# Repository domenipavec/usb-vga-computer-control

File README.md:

# usb-vga-computer-control

## Installation

`sudo apt-get install python-opencv v4l-utils python-pip`
`sudo pip install -r python-software/requirements.txt`

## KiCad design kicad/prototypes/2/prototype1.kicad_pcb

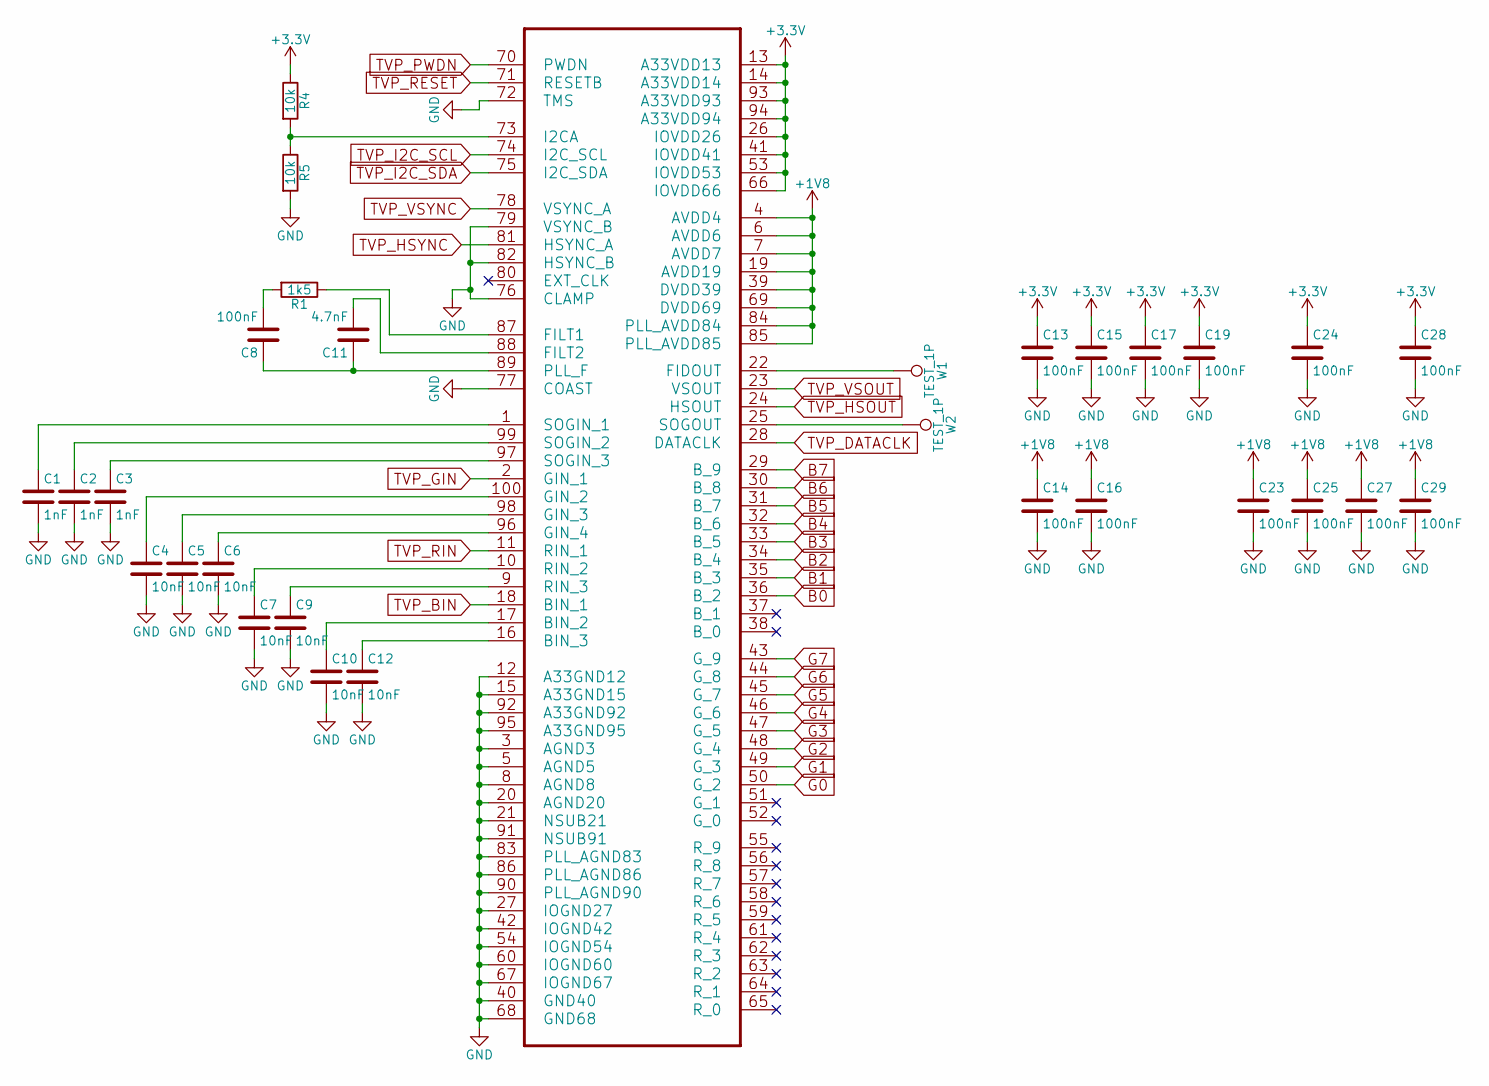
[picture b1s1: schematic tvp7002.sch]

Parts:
C1, C2, C3: 1nF; C_0402
C4, C5, C6, C7, C9, C10, C12: 10nF; C_0402
C8, C13, C14, C15, C16, C17, C19, C23, C24, C25, C27, C28, C29: 100nF; C_0402
C11: 4.7nF; C_0805
R1: 1k5; R_0805
R4, R5: 10k; R_0805
U1: TVP7002; LQFP-100_14x14mm_Pitch0.5mm
W1, W2: TEST_1P; Measurement_Point_Round-SMD-Pad_Small

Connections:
+1V8: C14.1, C16.1, C23.1, C25.1, C27.1, C29.1, U1.4 (AVDD4), U1.6 (AVDD6), U1.7 (AVDD7), U1.19 (AVDD19), U1.39 (DVDD39), U1.69 (DVDD69), U1.84 (PLL_AVDD84), U1.85 (PLL_AVDD85); also elsewhere on the board
+3V3: C13.1, C15.1, C17.1, C19.1, C24.1, C28.1, R4.1, U1.13 (A33VDD13), U1.14 (A33VDD14), U1.26 (IOVDD26), U1.41 (IOVDD41), U1.53 (IOVDD53), U1.66 (IOVDD66), U1.93 (A33VDD93), U1.94 (A33VDD94); also elsewhere on the board
B0: U1.36 (B_2); also elsewhere on the board
B1: U1.35 (B_3); also elsewhere on the board
B2: U1.34 (B_4); also elsewhere on the board
B3: U1.33 (B_5); also elsewhere on the board
B4: U1.32 (B_6); also elsewhere on the board
B5: U1.31 (B_7); also elsewhere on the board
B6: U1.30 (B_8); also elsewhere on the board
B7: U1.29 (B_9); also elsewhere on the board
G0: U1.50 (G_2); also elsewhere on the board
G1: U1.49 (G_3); also elsewhere on the board
G2: U1.48 (G_4); also elsewhere on the board
G3: U1.47 (G_5); also elsewhere on the board
G4: U1.46 (G_6); also elsewhere on the board
G5: U1.45 (G_7); also elsewhere on the board
G6: U1.44 (G_8); also elsewhere on the board
G7: U1.43 (G_9); also elsewhere on the board
GND: C1.2, C2.2, C3.2, C4.2, C5.2, C6.2, C7.2, C9.2, C10.2, C12.2, C13.2, C14.2, C15.2, C16.2, C17.2, C19.2, C23.2, C24.2, C25.2, C27.2, C28.2, C29.2, R5.2, U1.3 (AGND3), U1.5 (AGND5), U1.8 (AGND8), U1.12 (A33GND12), U1.15 (A33GND15), U1.20 (AGND20), U1.21 (NSUB21), U1.27 (IOGND27), U1.40 (GND40), U1.42 (IOGND42), U1.54 (IOGND54), U1.60 (IOGND60), U1.67 (IOGND67), U1.68 (GND68), U1.72 (TMS), U1.76 (CLAMP), U1.77 (COAST), U1.79 (VSYNC_B), U1.82 (HSYNC_B), U1.83 (PLL_AGND83), U1.86 (PLL_AGND86), U1.90 (PLL_AGND90), U1.91 (NSUB91), U1.92 (A33GND92), U1.95 (A33GND95); also elsewhere on the board
unnamed: C1.1, U1.1 (SOGIN_1)
unnamed: C2.1, U1.99 (SOGIN_2)
unnamed: C3.1, U1.97 (SOGIN_3)
unnamed: C4.1, U1.100 (GIN_2)
unnamed: C5.1, U1.98 (GIN_3)
unnamed: C6.1, U1.96 (GIN_4)
unnamed: C7.1, U1.10 (RIN_2)
unnamed: C8.2, R1.2
unnamed: C9.1, U1.9 (RIN_3)
unnamed: C10.1, U1.17 (BIN_2)
unnamed: C8.1, C11.1, U1.89 (PLL_F)
unnamed: C11.2, U1.88 (FILT2)
unnamed: C12.1, U1.16 (BIN_3)
unnamed: R1.1, U1.87 (FILT1)
unnamed: R4.2, R5.1, U1.73 (I2CA)
unnamed: U1.22 (FIDOUT), W1.1
unnamed: U1.25 (SOGOUT), W2.1
TVP_BIN: U1.18 (BIN_1); also elsewhere on the board
TVP_DATACLK: U1.28 (DATACLK); also elsewhere on the board
TVP_GIN: U1.2 (GIN_1); also elsewhere on the board
TVP_HSOUT: U1.24 (HSOUT); also elsewhere on the board
TVP_HSYNC: U1.81 (HSYNC_A); also elsewhere on the board
TVP_I2C_SCL: U1.74 (I2C_SCL); also elsewhere on the board
TVP_I2C_SDA: U1.75 (I2C_SDA); also elsewhere on the board
TVP_PWDN: U1.70 (PWDN); also elsewhere on the board
TVP_RESET: U1.71 (RESETB); also elsewhere on the board
TVP_RIN: U1.11 (RIN_1); also elsewhere on the board
TVP_VSOUT: U1.23 (VSOUT); also elsewhere on the board
TVP_VSYNC: U1.78 (VSYNC_A); also elsewhere on the board

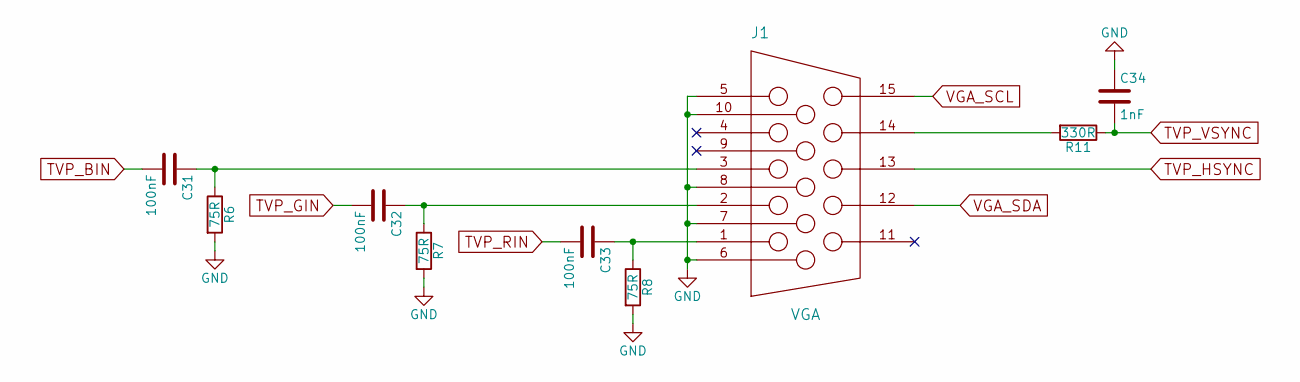
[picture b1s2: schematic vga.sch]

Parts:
C31, C32, C33: 100nF; C_0402
C34: 1nF; C_0402
J1: VGA
R6, R7, R8: 75R; R_0805
R11: 330R; R_0805

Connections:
AVR_MOSI: J1.12 (ID1/SDA); also elsewhere on the board
AVR_SCK: J1.15 (ID3/SCL); also elsewhere on the board
GND: C34.1, J1.5 (GND_HSYNC), J1.6 (RED_RTN), J1.7 (GREEN_RTN), J1.8 (BLUE_RTN), J1.10 (GND_VSYNC), R6.2, R7.2, R8.2; also elsewhere on the board
unnamed: C31.1, J1.3 (BLUE), R6.1
unnamed: C32.1, J1.2 (GREEN), R7.1
unnamed: C33.1, J1.1 (RED), R8.1
unnamed: J1.14 (VSYNC), R11.2
TVP_BIN: C31.2; also elsewhere on the board
TVP_GIN: C32.2; also elsewhere on the board
TVP_HSYNC: J1.13 (HSYNC); also elsewhere on the board
TVP_RIN: C33.2; also elsewhere on the board
TVP_VSYNC: C34.2, R11.1; also elsewhere on the board

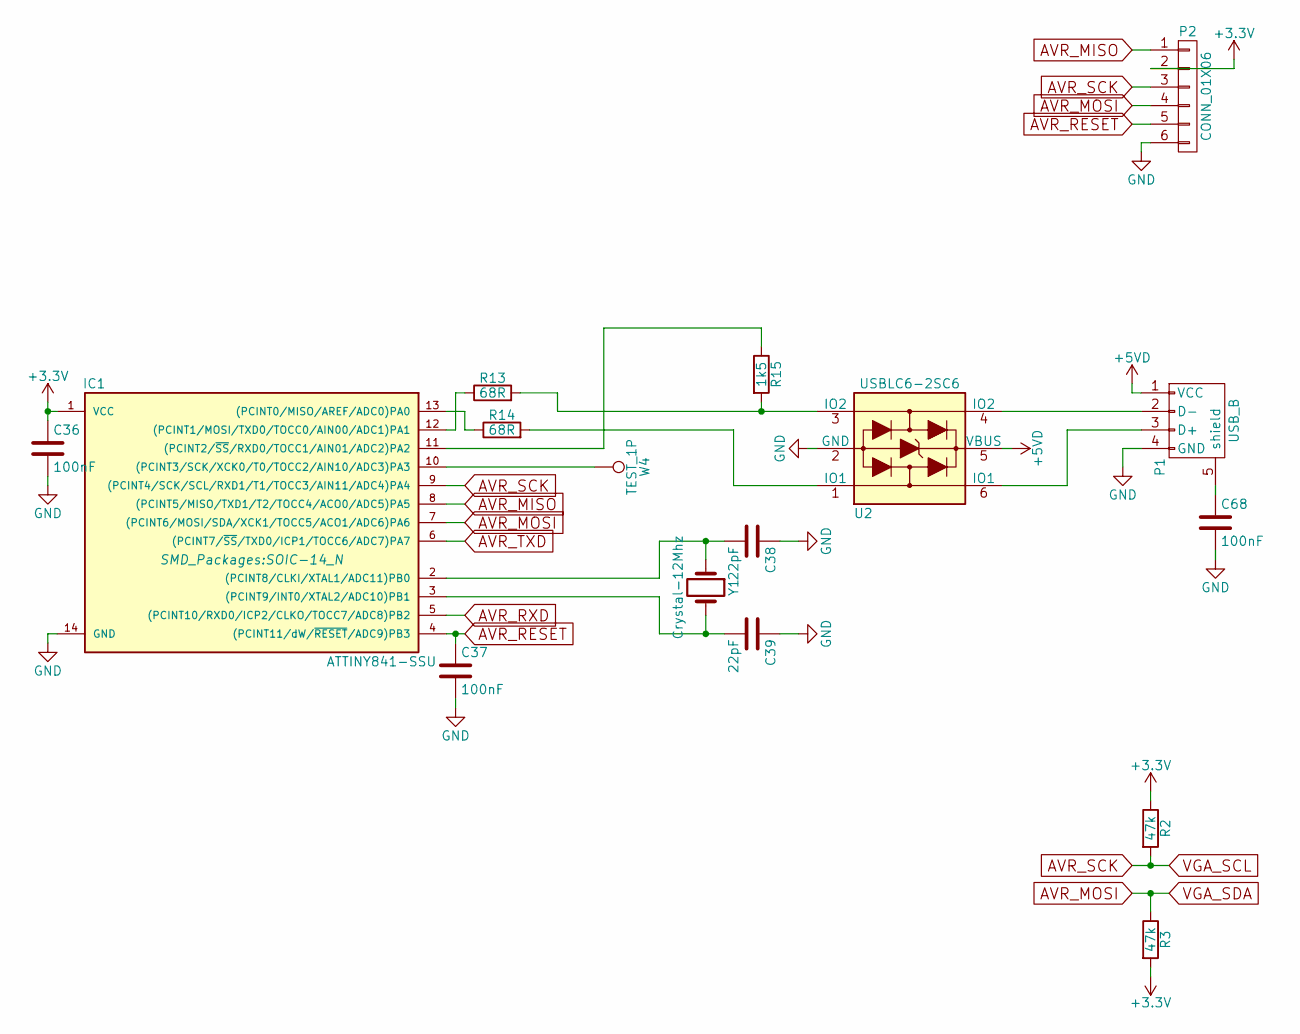
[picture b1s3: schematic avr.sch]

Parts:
C36, C37, C68: 100nF; C_0402
C38, C39: 22pF; C_0805
IC1: ATTINY841-SSU; SOIC-14_N
P1: USB_B
P2: CONN_01X06; ATTINY841-SPI
R2, R3: 47k; R_0805
R13, R14: 68R; R_0805
R15: 1k5; R_0805
U2: USBLC6-2SC6; SOT-23-6
W4: TEST_1P; Measurement_Point_Round-SMD-Pad_Small
Y1: Crystal-12Mhz; Crystal_HC49-U_Vertical

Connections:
+3V3: C36.1, IC1.1 (VCC), P2.2, R2.1, R3.2; also elsewhere on the board
+5VD: P1.1 (VCC), U2.5 (VBUS)
AVR_MISO: IC1.8 ((PCINT5/MISO/TXD1/T2/TOCC4/ACO0/ADC5)PA5), P2.1
AVR_MOSI: IC1.7 ((PCINT6/MOSI/SDA/XCK1/TOCC5/ACO1/ADC6)P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), P2.4, R3.1; also elsewhere on the board
AVR_RESET: C37.1, IC1.4 ((PCINT11/dW/~RESET~/ADC9)PB3), P2.5
AVR_RXD: IC1.5 ((PCINT10/RXD0/ICP2/CLKO/TOCC7/ADC8)PB2); also elsewhere on the board
AVR_SCK: IC1.9 ((PCINT4/SCK/SCL/RXD1/T1/TOCC3/AIN11/ADC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), P2.3, R2.2; also elsewhere on the board
AVR_TXD: IC1.6 ((PCINT7/~SS~/TXD0/ICP1/TOCC6/ADC7)PA7); also elsewhere on the board
GND: C36.2, C37.2, C38.1, C39.1, C68.2, IC1.14 (GND), P1.4 (GND), P2.6, U2.2 (GND); also elsewhere on the board
unnamed: C38.2, IC1.2 ((PCINT8/CLKI/XTAL1/ADC11)PB0), Y1.1
unnamed: C39.2, IC1.3 ((PCINT9/INT0/XTAL2/ADC10)PB1), Y1.2
unnamed: C68.1, P1.5 (shield)
unnamed: IC1.10 ((PCINT3/SCK/XCK0/T0/TOCC2/AIN10/ADC3)PA3), W4.1
unnamed: IC1.11 ((PCINT2/~SS~/RXD0/TOCC1/AIN01/ADC2)PA2), R15.1
unnamed: IC1.12 ((PCINT1/MOSI/TXD0/TOCC0/AIN00/ADC1)PA1), R13.1
unnamed: IC1.13 ((PCINT0/MISO/AREF/ADC0)PA0), R14.1
unnamed: P1.2 (D-), U2.4 (IO2)
unnamed: P1.3 (D+), U2.6 (IO1)
unnamed: R13.2, R15.2, U2.3 (IO2)
unnamed: R14.2, U2.1 (IO1)

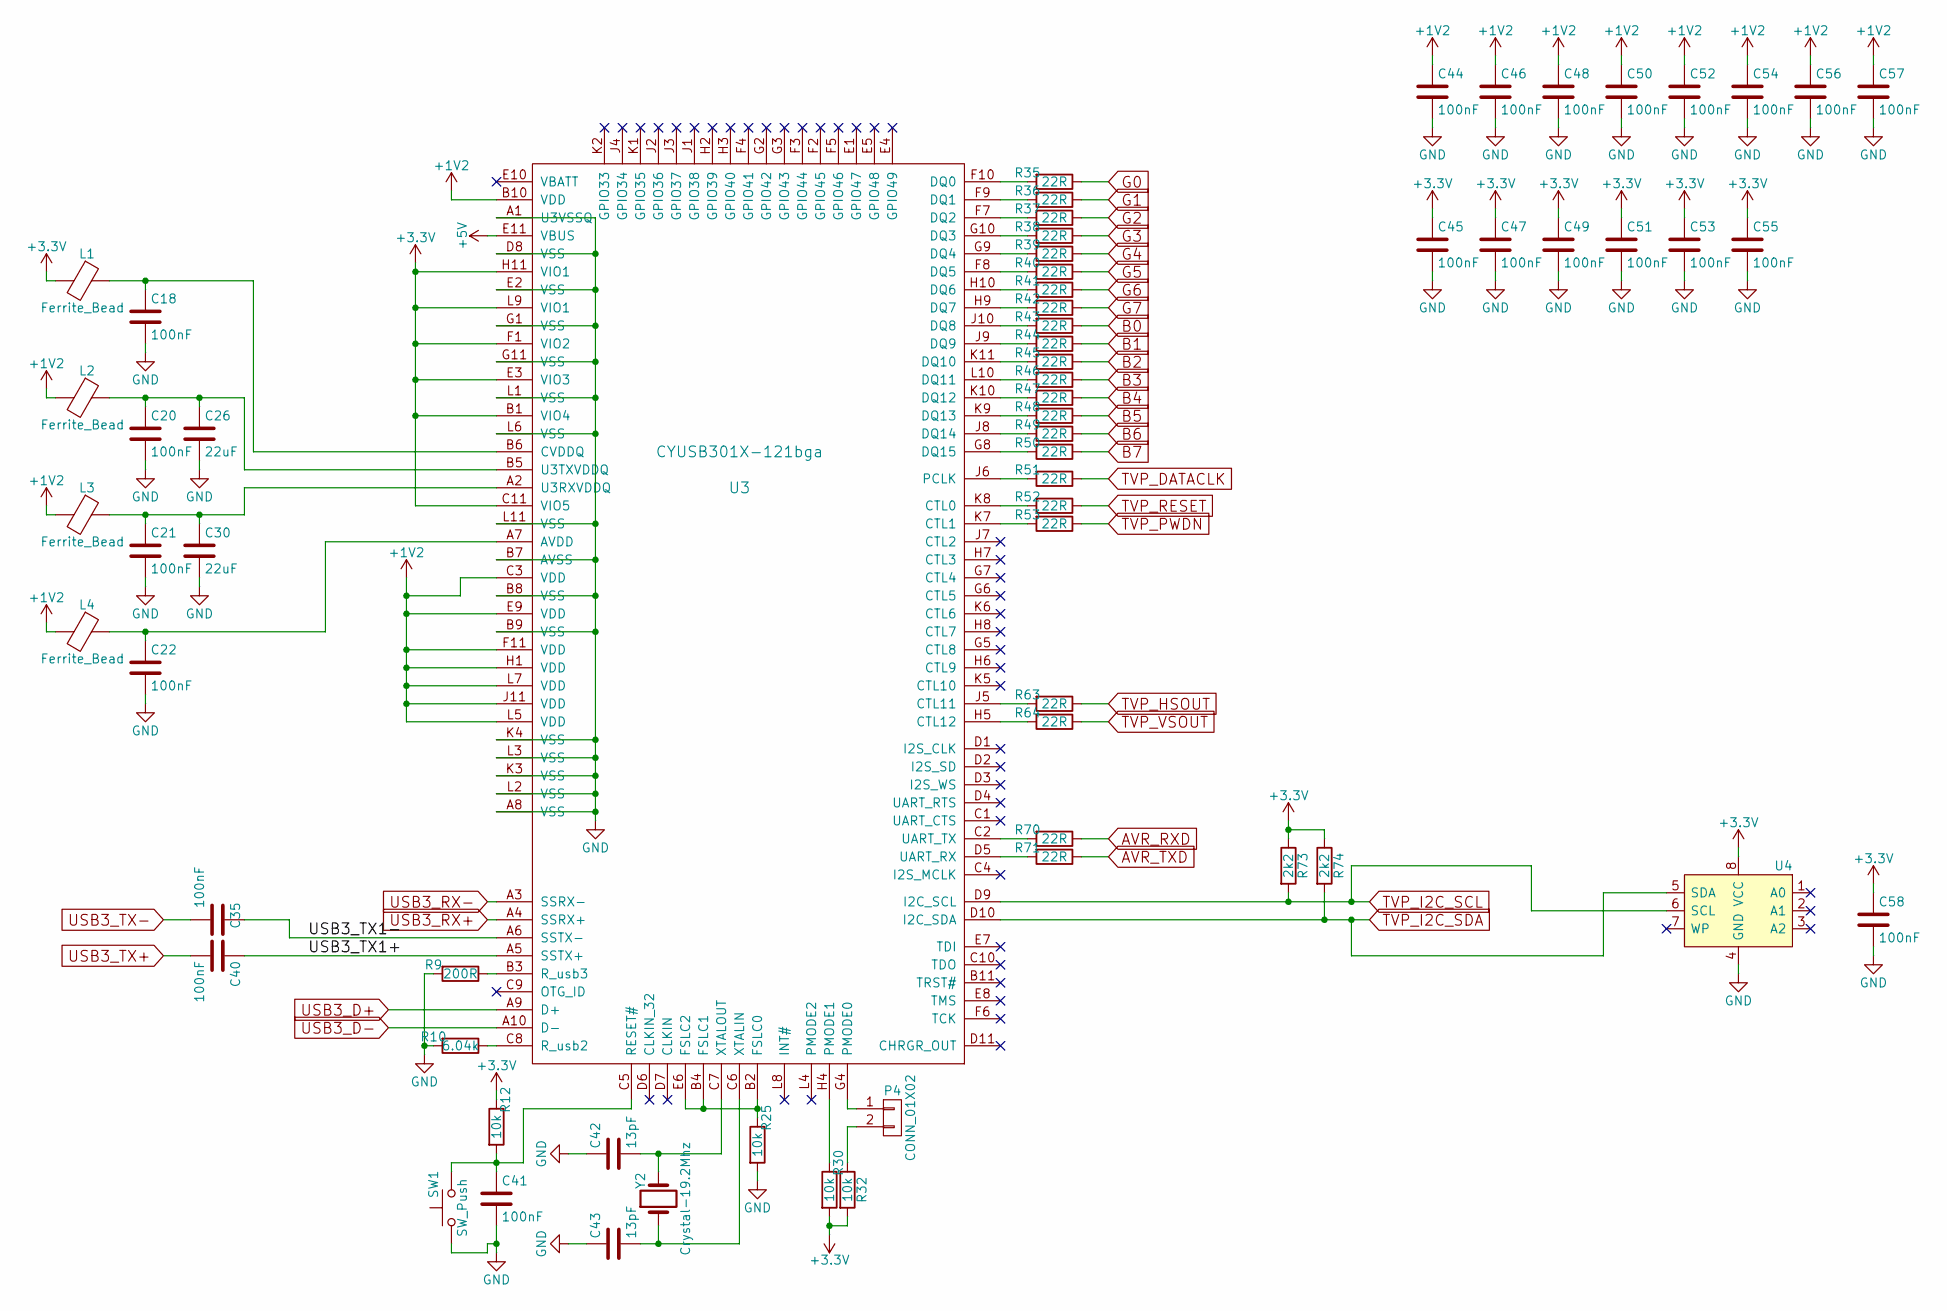
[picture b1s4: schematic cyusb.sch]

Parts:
C18, C20, C21, C22, C35, C40, C41, C44, C45, C46, C47, C48, C49, C50, C51, C52, C53, C54, C55, C56, C57, C58: 100nF; C_0402
C26, C30: 22uF; C_1206
C42, C43: 13pF; C_0805
L1, L2, L3, L4: Ferrite_Bead; R_0805
P4: CONN_01X02; Socket_Strip_Straight_1x02
R9: 200R; R_0402
R10: 6.04k; R_0402
R12, R25, R30, R32: 10k; R_0805
R35, R36, R37, R38, R39, R40, R41, R42, R43, R44, R45, R46, R47, R48, R49, R50, R51, R52, R53, R63, R64, R70, R71: 22R; R_0402
R73, R74: 2k2; R_0805
SW1: SW_Push; pushbutton
U3: CYUSB301X-121bga; BGA_121
U4: 24LC16; SOIC-8_3.9x4.9mm_Pitch1.27mm
Y2: Crystal-19.2Mhz; Crystal_HC49-U_Vertical

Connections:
+1V2: C44.1, C46.1, C48.1, C50.1, C52.1, C54.1, C56.1, C57.1, L2.2, L3.2, L4.2, U3.B10 (VDD), U3.C3 (VDD), U3.E9 (VDD), U3.F11 (VDD), U3.H1 (VDD), U3.J11 (VDD), U3.L5 (VDD), U3.L7 (VDD); also elsewhere on the board
+3V3: C45.1, C47.1, C49.1, C51.1, C53.1, C55.1, C58.1, L1.2, R12.1, R30.2, R32.2, R73.1, R74.1, U3.B1 (VIO4), U3.C11 (VIO5), U3.E3 (VIO3), U3.F1 (VIO2), U3.H11 (VIO1), U3.L9 (VIO1), U4.8 (VCC); also elsewhere on the board
+5V: U3.E11 (VBUS); also elsewhere on the board
/cyusb/USB3_TX1+: C40.1, U3.A5 (SSTX+)
/cyusb/USB3_TX1-: C35.1, U3.A6 (SSTX-)
AVR_RXD: R70.1; also elsewhere on the board
AVR_TXD: R71.1; also elsewhere on the board
B0: R43.1; also elsewhere on the board
B1: R44.1; also elsewhere on the board
B2: R45.1; also elsewhere on the board
B3: R46.1; also elsewhere on the board
B4: R47.1; also elsewhere on the board
B5: R48.1; also elsewhere on the board
B6: R49.1; also elsewhere on the board
B7: R50.1; also elsewhere on the board
G0: R35.1; also elsewhere on the board
G1: R36.1; also elsewhere on the board
G2: R37.1; also elsewhere on the board
G3: R38.1; also elsewhere on the board
G4: R39.1; also elsewhere on the board
G5: R40.1; also elsewhere on the board
G6: R41.1; also elsewhere on the board
G7: R42.1; also elsewhere on the board
GND: C18.2, C20.2, C21.2, C22.2, C26.2, C30.2, C41.2, C42.1, C43.1, C44.2, C45.2, C46.2, C47.2, C48.2, C49.2, C50.2, C51.2, C52.2, C53.2, C54.2, C55.2, C56.2, C57.2, C58.2, R9.2, R10.2, R25.2, SW1.1, U3.A1 (U3VSSQ), U3.A8 (VSS), U3.B7 (AVSS), U3.B8 (VSS), U3.B9 (VSS), U3.D8 (VSS), U3.E2 (VSS), U3.G1 (VSS), U3.G11 (VSS), U3.K3 (VSS), U3.K4 (VSS), U3.L1 (VSS), U3.L2 (VSS), U3.L3 (VSS), U3.L6 (VSS), U3.L11 (VSS), U4.4 (GND); also elsewhere on the board
unnamed: C18.1, L1.1, U3.B6 (CVDDQ)
unnamed: C20.1, C26.1, L2.1, U3.B5 (U3TXVDDQ)
unnamed: C21.1, C30.1, L3.1, U3.A2 (U3RXVDDQ)
unnamed: C22.1, L4.1, U3.A7 (AVDD)
unnamed: C41.1, R12.2, SW1.2, U3.C5 (RESET#)
unnamed: C42.2, U3.C7 (XTALOUT), Y2.2
unnamed: C43.2, U3.C6 (XTALIN), Y2.1
unnamed: P4.1, U3.G4 (PMODE0)
unnamed: P4.2, R32.1
unnamed: R9.1, U3.B3 (R_usb3)
unnamed: R10.1, U3.C8 (R_usb2)
unnamed: R25.1, U3.B2 (FSLC0), U3.B4 (FSLC1), U3.E6 (FSLC2)
unnamed: R30.1, U3.H4 (PMODE1)
unnamed: R35.2, U3.F10 (DQ0)
unnamed: R36.2, U3.F9 (DQ1)
unnamed: R37.2, U3.F7 (DQ2)
unnamed: R38.2, U3.G10 (DQ3)
unnamed: R39.2, U3.G9 (DQ4)
unnamed: R40.2, U3.F8 (DQ5)
unnamed: R41.2, U3.H10 (DQ6)
unnamed: R42.2, U3.H9 (DQ7)
unnamed: R43.2, U3.J10 (DQ8)
unnamed: R44.2, U3.J9 (DQ9)
unnamed: R45.2, U3.K11 (DQ10)
unnamed: R46.2, U3.L10 (DQ11)
unnamed: R47.2, U3.K10 (DQ12)
unnamed: R48.2, U3.K9 (DQ13)
unnamed: R49.2, U3.J8 (DQ14)
unnamed: R50.2, U3.G8 (DQ15)
unnamed: R51.2, U3.J6 (PCLK)
unnamed: R52.2, U3.K8 (CTL0)
unnamed: R53.2, U3.K7 (CTL1)
unnamed: R63.2, U3.J5 (CTL11)
unnamed: R64.2, U3.H5 (CTL12)
unnamed: R70.2, U3.C2 (UART_TX)
unnamed: R71.2, U3.D5 (UART_RX)
TVP_DATACLK: R51.1; also elsewhere on the board
TVP_HSOUT: R63.1; also elsewhere on the board
TVP_I2C_SCL: R73.2, U3.D9 (I2C_SCL), U4.6 (SCL); also elsewhere on the board
TVP_I2C_SDA: R74.2, U3.D10 (I2C_SDA), U4.5 (SDA); also elsewhere on the board
TVP_PWDN: R53.1; also elsewhere on the board
TVP_RESET: R52.1; also elsewhere on the board
TVP_VSOUT: R64.1; also elsewhere on the board
USB3_D+: U3.A9 (D+); also elsewhere on the board
USB3_D-: U3.A10 (D-); also elsewhere on the board
USB3_RX+: U3.A4 (SSRX+); also elsewhere on the board
USB3_RX-: U3.A3 (SSRX-); also elsewhere on the board
USB3_TX+: C40.2; also elsewhere on the board
USB3_TX-: C35.2; also elsewhere on the board

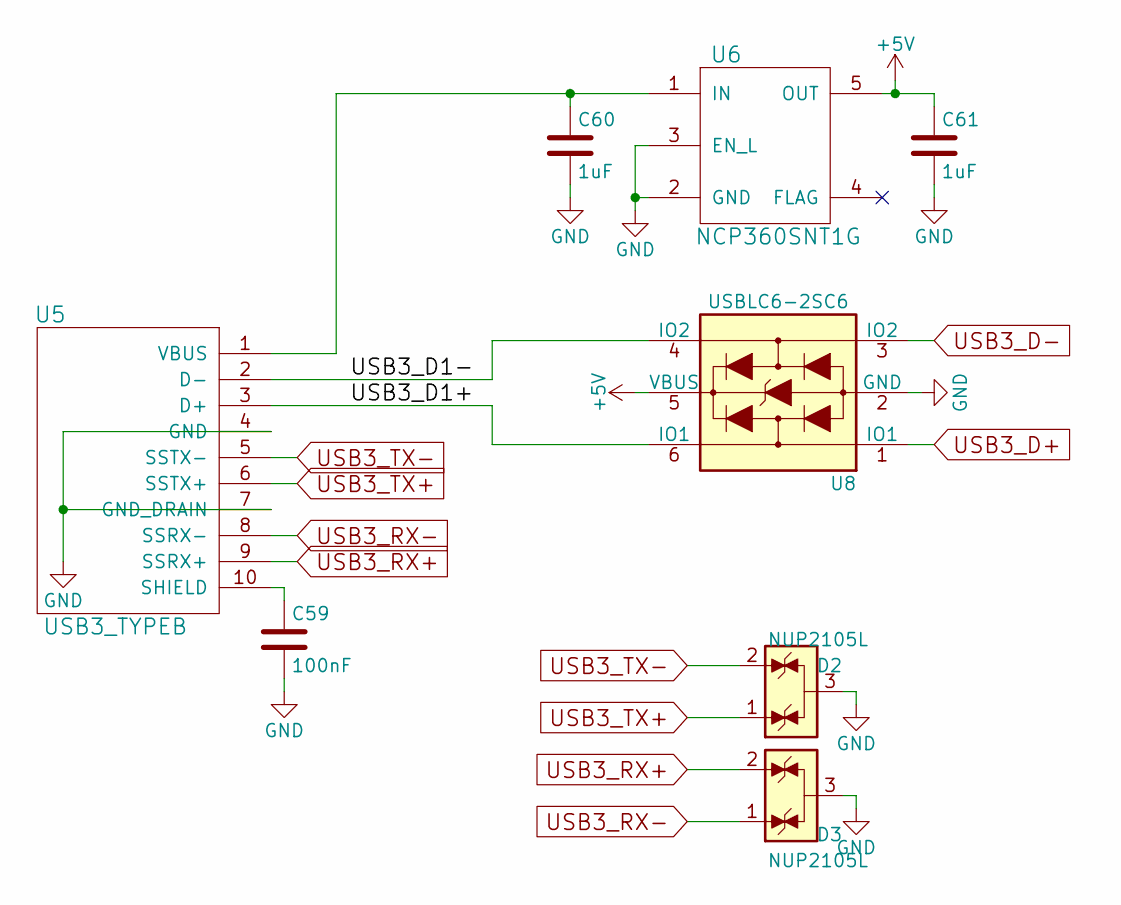
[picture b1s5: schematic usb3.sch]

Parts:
C59: 100nF; C_0402
C60, C61: 1uF; C_0805
D2, D3: NUP2105L; DRT
U5: USB3_TYPEB; USB3_TYPE_B
U6: NCP360SNT1G; SOT-23-5
U8: USBLC6-2SC6; SOT-23-6

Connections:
+5V: C61.1, U6.5 (OUT), U8.5 (VBUS); also elsewhere on the board
/usb3/USB3_D1+: U5.3 (D+), U8.6 (IO1)
/usb3/USB3_D1-: U5.2 (D-), U8.4 (IO2)
GND: C59.2, C60.2, C61.2, D2.3 (A), D3.3 (A), U5.4 (GND), U5.7 (GND_DRAIN), U6.2 (GND), U6.3 (EN_L), U8.2 (GND); also elsewhere on the board
unnamed: C59.1, U5.10 (SHIELD)
unnamed: C60.1, U5.1 (VBUS), U6.1 (IN)
USB3_D+: U8.1 (IO1); also elsewhere on the board
USB3_D-: U8.3 (IO2); also elsewhere on the board
USB3_RX+: D3.2 (K), U5.9 (SSRX+); also elsewhere on the board
USB3_RX-: D3.1 (K), U5.8 (SSRX-); also elsewhere on the board
USB3_TX+: D2.1 (K), U5.6 (SSTX+); also elsewhere on the board
USB3_TX-: D2.2 (K), U5.5 (SSTX-); also elsewhere on the board

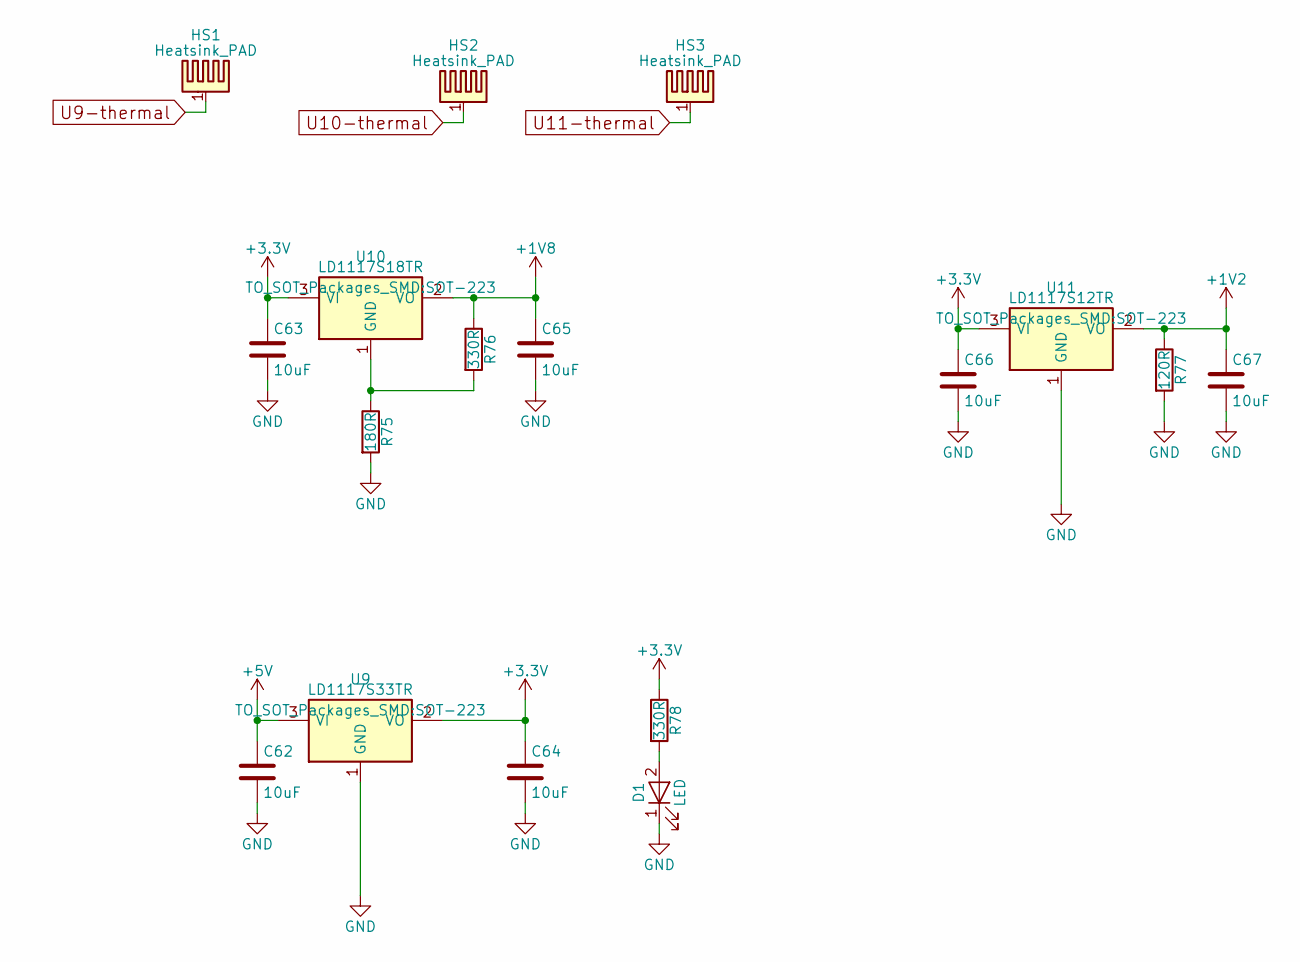
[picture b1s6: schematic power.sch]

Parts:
C62, C63, C64, C65, C66, C67: 10uF; C_0805
D1: LED; LED-3MM
HS1, HS2, HS3: Heatsink_PAD; Measurement_Point_Round-SMD-Pad_Small
R75: 180R; R_0805
R76, R78: 330R; R_0805
R77: 120R; R_0805
U9: LD1117S33TR; SOT-223
U10: LD1117S18TR; SOT-223
U11: LD1117S12TR; SOT-223

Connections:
+1V2: C67.1, R77.1, U11.2 (VO); also elsewhere on the board
+1V8: C65.1, R76.1, U10.2 (VO); also elsewhere on the board
+3V3: C63.1, C64.1, C66.1, R78.1, U9.2 (VO), U10.3 (VI), U11.3 (VI); also elsewhere on the board
+5V: C62.1, U9.3 (VI); also elsewhere on the board
GND: C62.2, C63.2, C64.2, C65.2, C66.2, C67.2, D1.1 (K), R75.2, R77.2, U9.1 (GND), U11.1 (GND); also elsewhere on the board
unnamed: D1.2 (A), R78.2
unnamed: R75.1, R76.2, U10.1 (GND)
U9-thermal: U9.4
U10-thermal: U10.4
U11-thermal: U11.4

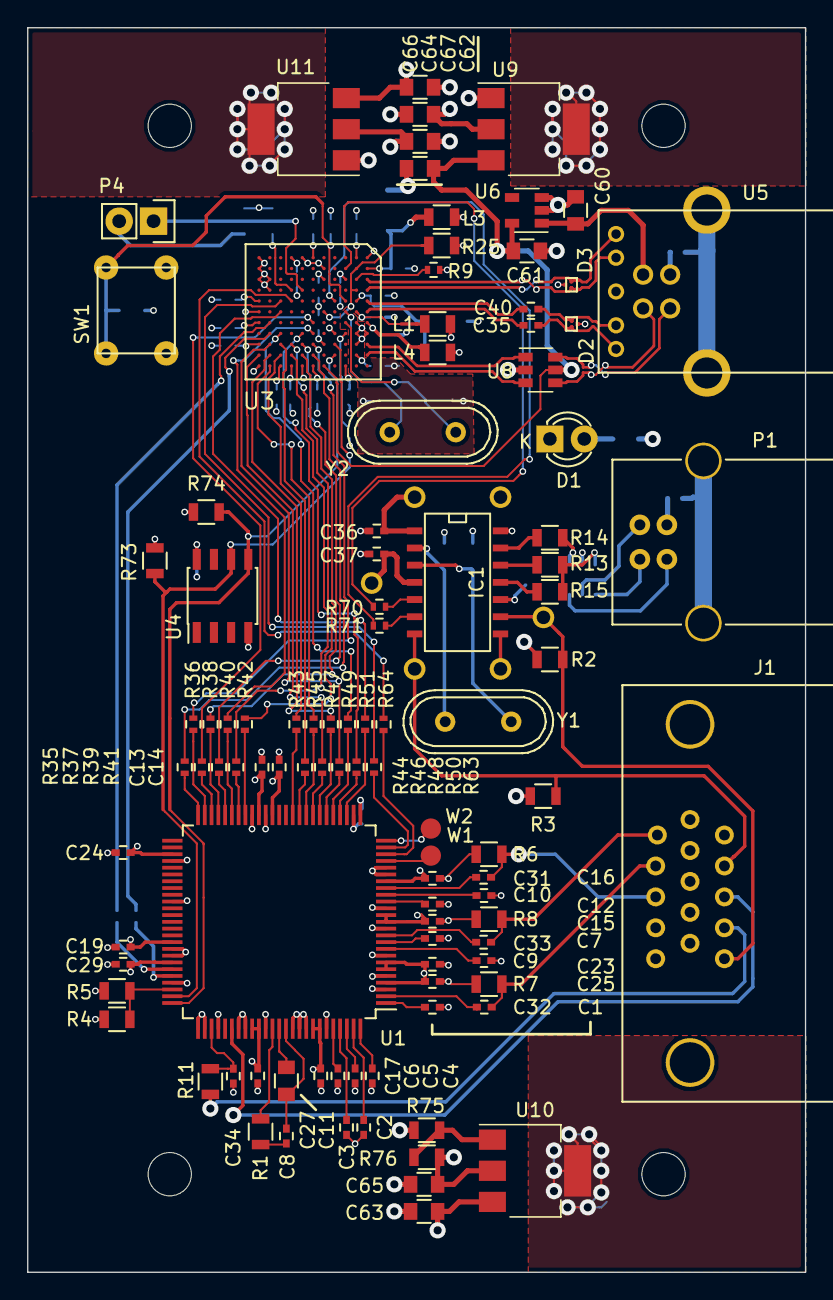
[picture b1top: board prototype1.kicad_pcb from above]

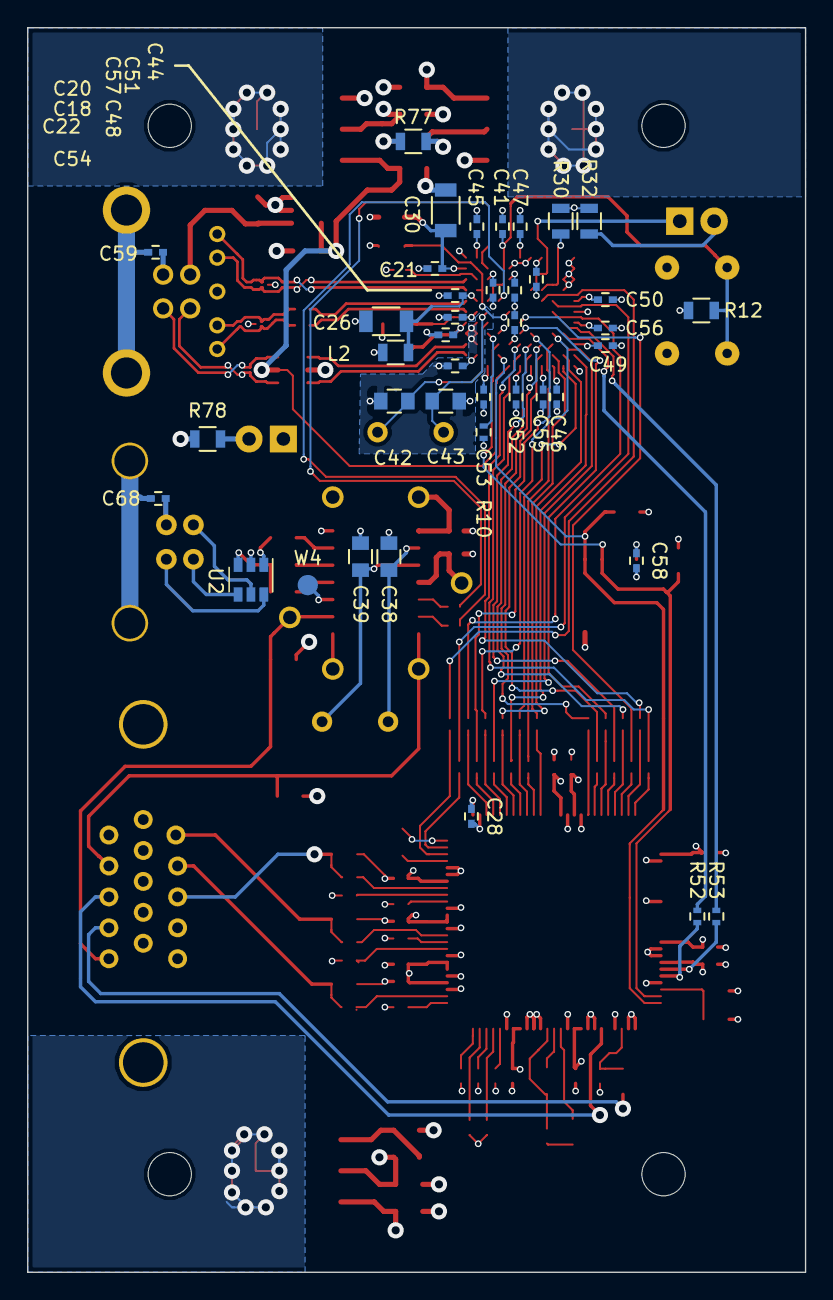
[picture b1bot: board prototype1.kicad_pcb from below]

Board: 4 copper layers, 57.5 x 92.0 mm, 143 parts (41 on the bottom side), 122 nets.

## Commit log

2016-12-07 First prototype pcb
2016-12-07 Example project with tvp init, not working
2016-12-07 Remove usb debug endpoint
2016-12-07 Remove camera ptzcontrol code
2016-12-07 Remove support for brightness
2016-12-08 Added xml files
2016-12-08 Copy of example state machine
2016-12-13 Sort of working gpif for vga, do not have much blue for some reason
2016-12-13 Simple cv show video
2016-12-17 Working hid mouse with mostly example code
2016-12-20 Added power control i2c command
2016-12-28 Rename vgascript
2016-12-28 Control mouse with uart
2016-12-29 Moved kicad files
2016-12-29 Added edid to avr
2016-12-29 Added uart-script
2016-12-29 Updated to new kicad
2017-01-03 Final prototype 2 board
2017-01-03 Create img file with makefile, dos2unix
2017-01-03 Set hsout for zero horizontal borders
2017-01-03 dos2unix
2017-01-03 Fix vga offset
2017-01-06 Added string descriptors using usbgen
2017-01-07 usbgen for device descriptors
2017-01-07 Device qualifier and bos descriptors with usbgen
2017-01-08 usb configuration for fs and ss with usbgen
2017-01-08 Added uart descriptors
2017-01-09 Moved main function to main.c
2017-01-10 Moved thread creation to main.c
2017-01-10 Disable uart debug
2017-01-10 Handle usb requests based on target interface
2017-01-10 Format
2017-01-11 Working uart
2017-01-12 Working hid config
2017-01-12 Working mouse commands
2017-01-12 Added support for keyboard
2017-01-12 Generic uart script for command line messages
2017-01-12 Use pygame for keyup and keydown events
2017-01-13 Working keyboard
2017-01-15 Added config for pull up to pin
2017-01-15 Added requirements
2017-01-15 Added ability to choose video device
2017-01-15 Fix installation instructions
2018-02-05 Update for small device
2018-02-05 Added TODO
2019-10-11 Fixed typo
    Hi! I replaced the "Untill" with "Until", maybe it helps!
